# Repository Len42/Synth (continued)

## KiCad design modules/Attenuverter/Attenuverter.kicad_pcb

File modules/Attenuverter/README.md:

# Dual Attenuverter

## 4HP Eurorack Module

### Features
- Gain knob multiplies the input signal by 2 when turned to max and by -1 (i.e. inverted) when turned all the way down.
- Offset knob adds an offset voltage in the range of -5 V to +5 V.
- Channel 1's input is normalled from +5 V so it can be used as an adjustable CV source.
- Channel 2's input is normalled from channel 1's input.
- If channel 1's output is not patched, it is normalled to mix with channel 2's output. (Please note that this can cause unintended results if channel 2 is used without using channel 1.)

### Notes
For best results, the gain potentiometers (RV1 & RV3) should be very close to 100 kΩ. The pots specified for this project have a tolerance of 20% so I recommend measuring a few and selecting the most accurate ones.

PCB layouts are provided in KiCad and gerber formats. A PCB layout for a drilled front panel (with no labels) is also included.

The PCBs that I used can be ordered from OSH Park. The designs are here:
- [Front panel](https://oshpark.com/shared_projects/6utvepvX)
- [Controls board](https://oshpark.com/shared_projects/9pQK8wer)
- [Main board](https://oshpark.com/shared_projects/1qgK0ORb)

Please note that I am a hobbyist, not a trained electronics engineer. No guarantees!

### Software Used

* [KiCad](https://www.kicad.org/) 6.0.6

<hr /><div><div style="float:left; padding-right:10px;"></div><div style="xfloat:left; padding-left:10px;"><br />© 2022 Len Popp CC BY<br />This work is licensed under a <a rel="license" href="http://creativecommons.org/licenses/by/4.0/">Creative Commons Attribution 4.0 International License</a>.</div></div>

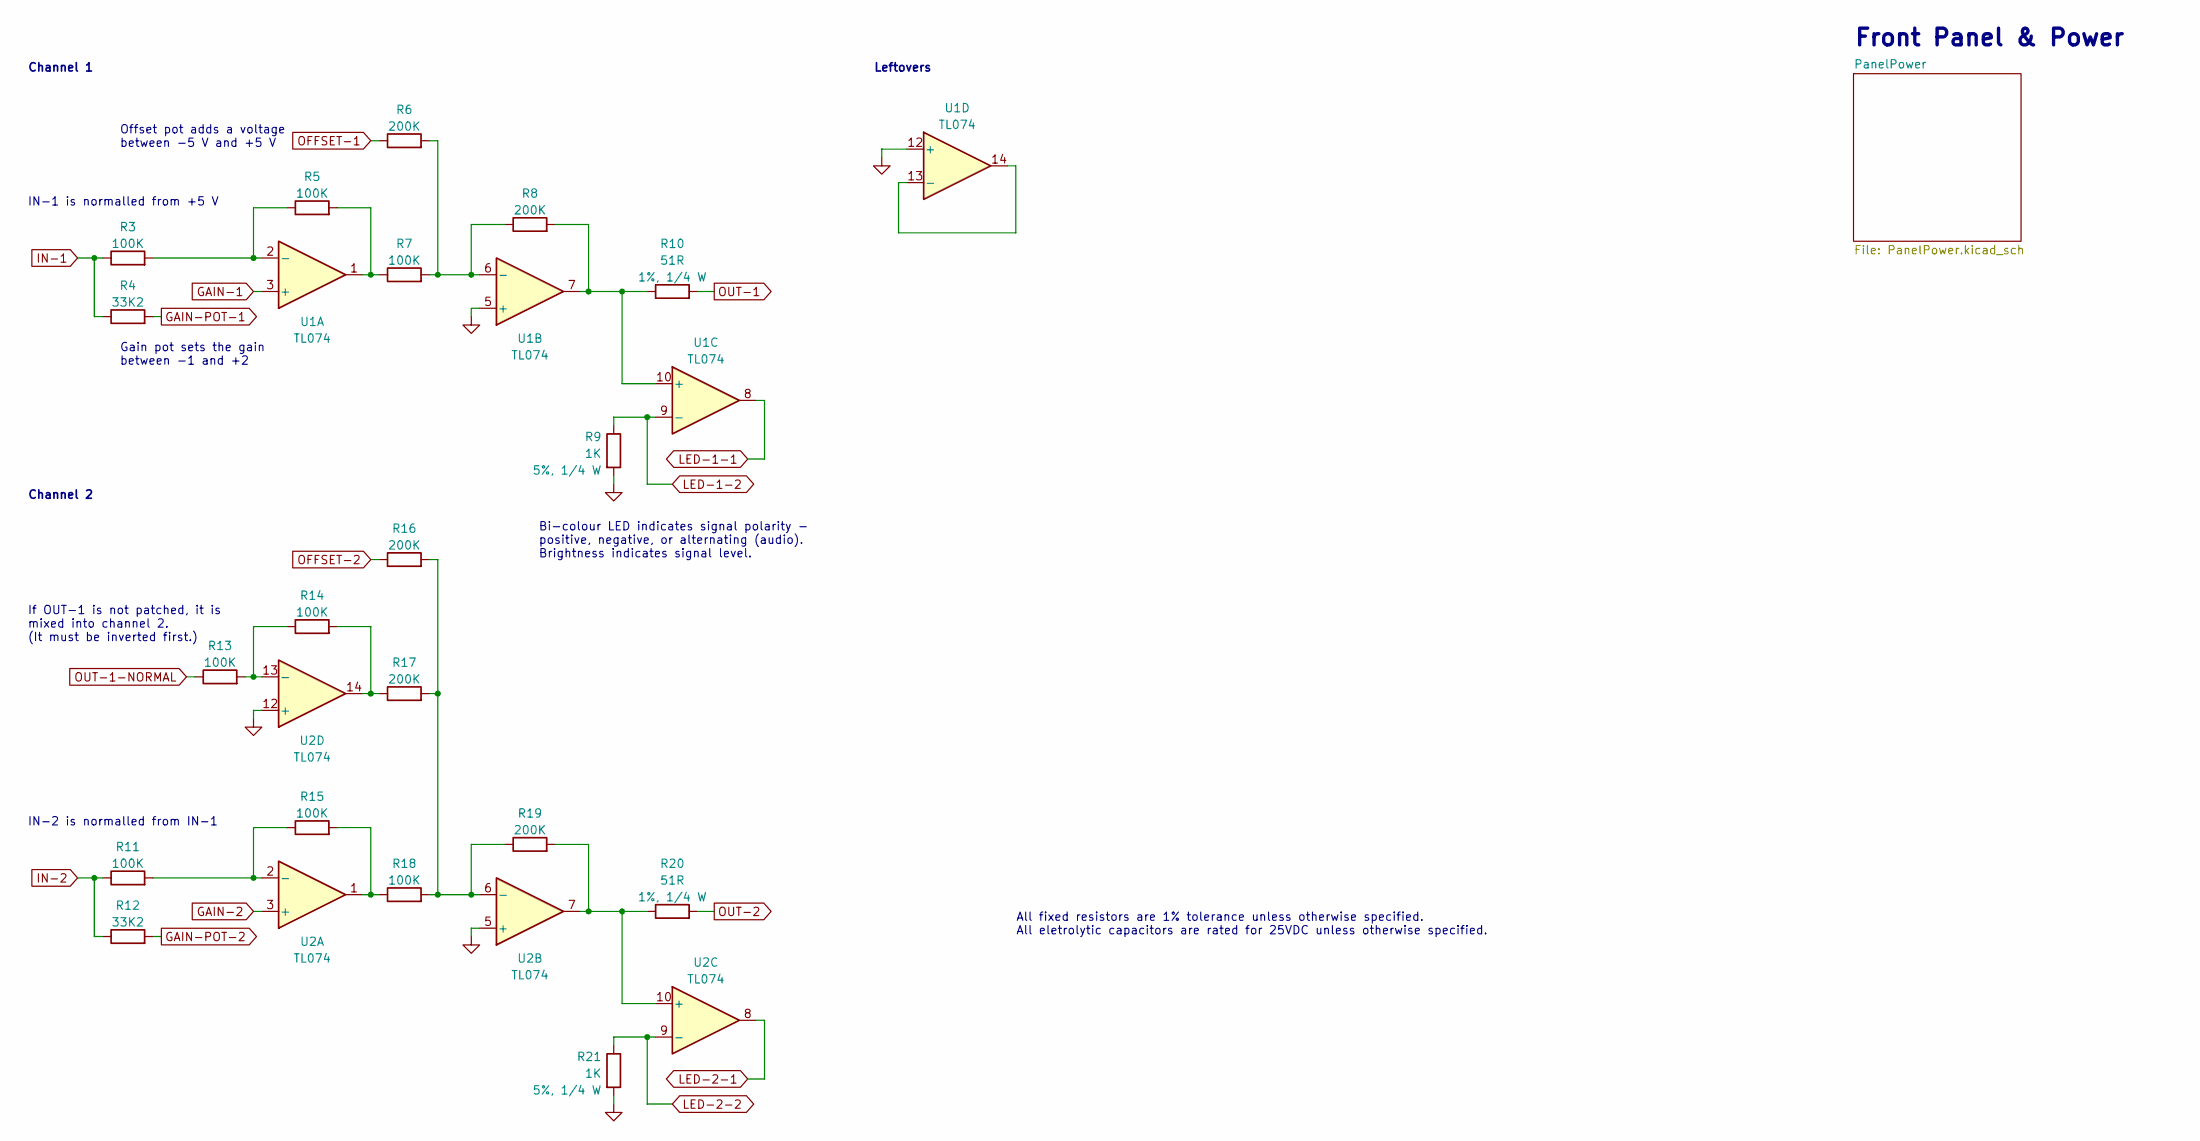
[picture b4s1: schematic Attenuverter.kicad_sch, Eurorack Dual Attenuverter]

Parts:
R3, R5, R7, R11, R13, R14, R15, R18: 100K; R_Axial_DIN0207_L6.3mm_D2.5mm_P7.62mm_Horizontal; ManufacturerPartNum MFR-12FRF52-100K
R4, R12: 33K2; R_Axial_DIN0207_L6.3mm_D2.5mm_P10.16mm_Horizontal; ManufacturerPartNum MFR-25FRF52-33K2
R6, R8, R16, R17, R19: 200K; R_Axial_DIN0207_L6.3mm_D2.5mm_P7.62mm_Horizontal; ManufacturerPartNum MFR-12FTF52-200K
R9, R21: 1K; R_Axial_DIN0207_L6.3mm_D2.5mm_P10.16mm_Horizontal; ManufacturerPartNum CCF071K00JKE36
R10, R20: 51R; R_Axial_DIN0207_L6.3mm_D2.5mm_P10.16mm_Horizontal; ManufacturerPartNum MFR-25FBF52-51R
U1, U2: TL074; DIP-14_W7.62mm; ManufacturerPartNum TL074BCN

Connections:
GAIN-1: U1.3 (+); also elsewhere on the board
GAIN-2: U2.3 (+); also elsewhere on the board
GAIN-POT-1: R4.2; also elsewhere on the board
GAIN-POT-2: R12.2; also elsewhere on the board
GND: R9.2, R21.2, U1.5 (+), U1.12 (+), U2.5 (+), U2.12 (+); also elsewhere on the board
IN-1: R3.1, R4.1; also elsewhere on the board
IN-2: R11.1, R12.1; also elsewhere on the board
LED-1-1: U1.8; also elsewhere on the board
LED-1-2: R9.1, U1.9 (-); also elsewhere on the board
LED-2-1: U2.8; also elsewhere on the board
LED-2-2: R21.1, U2.9 (-); also elsewhere on the board
unnamed: R3.2, R5.1, U1.2 (-)
unnamed: R5.2, R7.1, U1.1
unnamed: R6.2, R7.2, R8.1, U1.6 (-)
unnamed: R8.2, R10.1, U1.7, U1.10 (+)
unnamed: R11.2, R15.1, U2.2 (-)
unnamed: R13.2, R14.1, U2.13 (-)
unnamed: R14.2, R17.1, U2.14
unnamed: R15.2, R18.1, U2.1
unnamed: R16.2, R17.2, R18.2, R19.1, U2.6 (-)
unnamed: R19.2, R20.1, U2.7, U2.10 (+)
unnamed: U1.13 (-), U1.14
OFFSET-1: R6.1; also elsewhere on the board
OFFSET-2: R16.1; also elsewhere on the board
OUT-1: R10.2; also elsewhere on the board
OUT-1-NORMAL: R13.1; also elsewhere on the board
OUT-2: R20.2; also elsewhere on the board

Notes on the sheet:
IN-2 is normalled from IN-1
All fixed resistors are 1% tolerance unless otherwise specified. All eletrolytic capacitors are rated for 25VDC unless otherwise specified.
Bi-colour LED indicates signal polarity - positive, negative, or alternating (audio). Brightness indicates signal level.
Gain pot sets the gain between -1 and +2
IN-1 is normalled from +5 V
If OUT-1 is not patched, it is mixed into channel 2. (It must be inverted first.)
Front Panel & Power
Offset pot adds a voltage between -5 V and +5 V
Channel 1
Channel 2
Leftovers

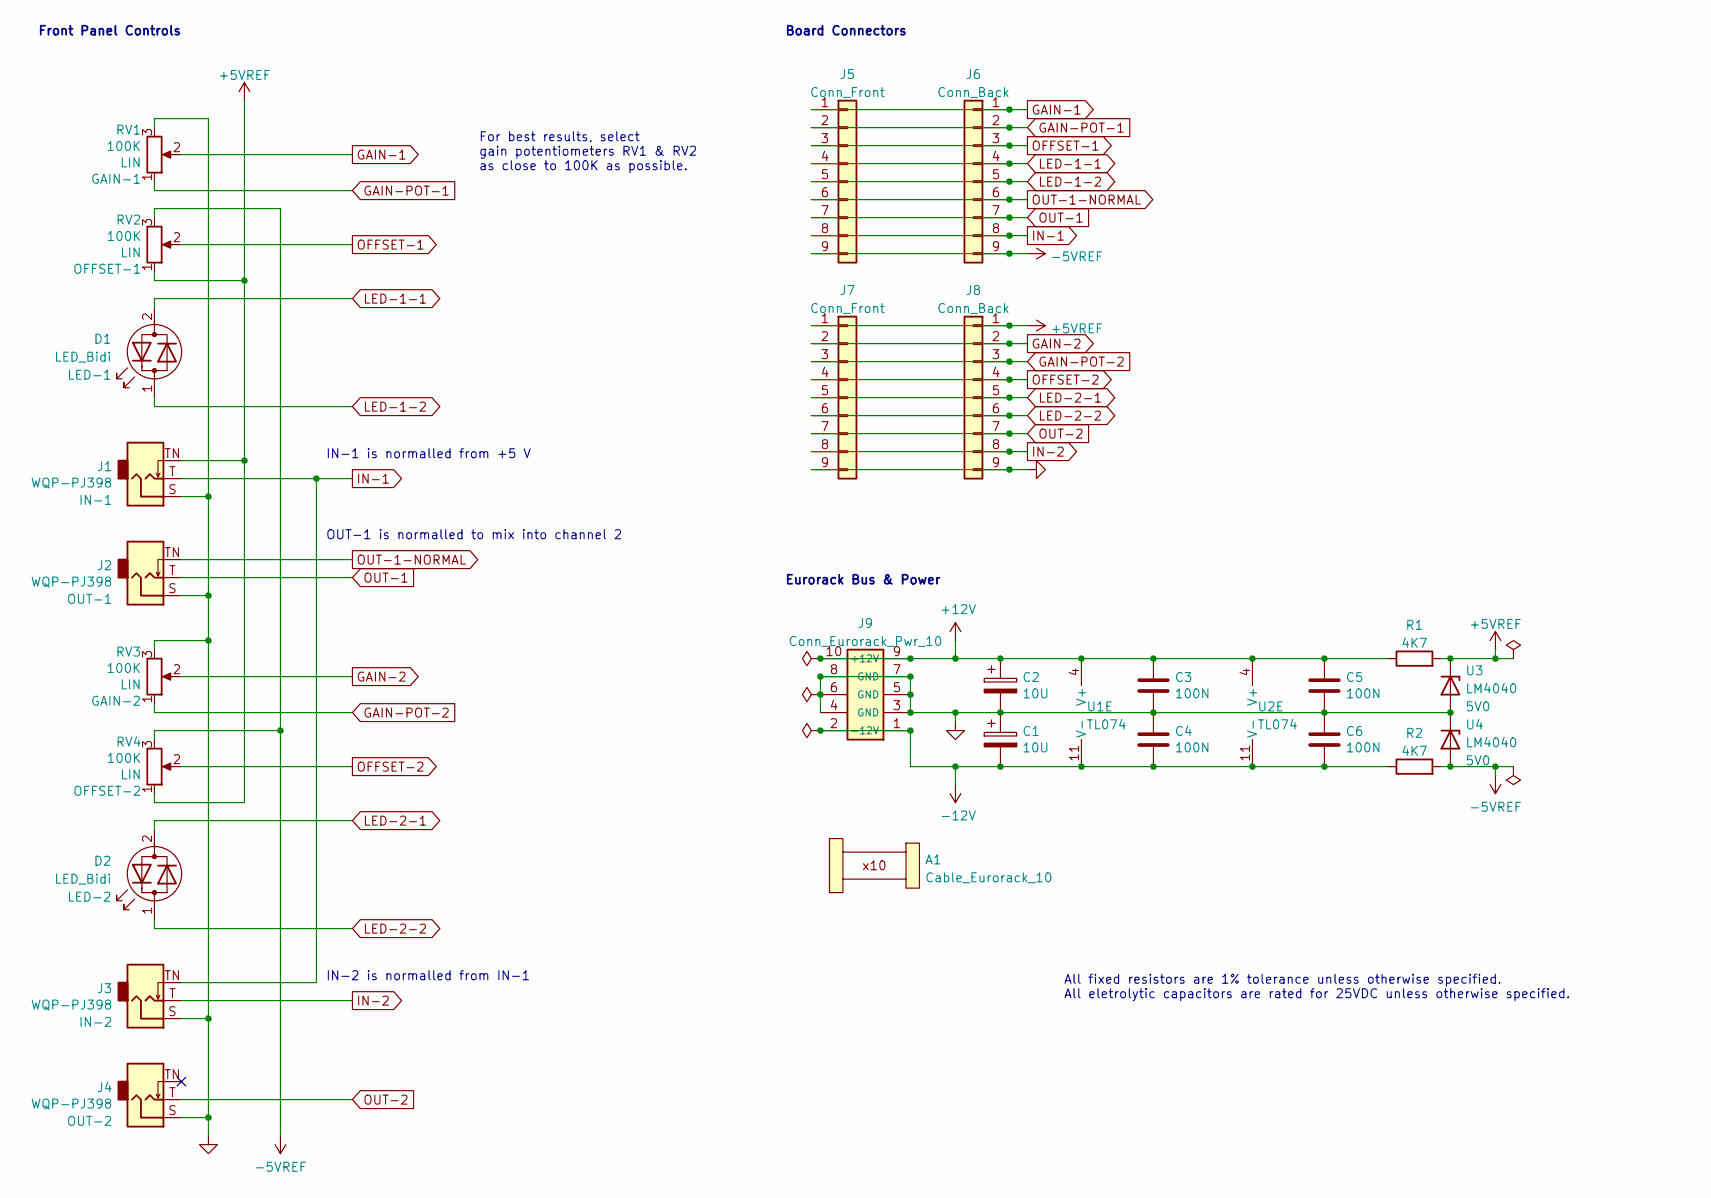
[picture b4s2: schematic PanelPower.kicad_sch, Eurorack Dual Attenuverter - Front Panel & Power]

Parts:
A1: Cable_Eurorack_10; NoFootprint
C1, C2: 10U; CP_Radial_D5.0mm_P2.50mm; ManufacturerPartNum ECE-A1VKS100I
C3, C4, C5, C6: 100N; C_Disc_D5.0mm_W2.5mm_P2.50mm; ManufacturerPartNum FG18X7R1H104KNT06
D1, D2: LED_Bidi; LED_D3.0mm; ManufacturerPartNum WP937GYW
J1, J2, J3, J4: WQP-PJ398; Jack_3.5mm_QingPu_WQP-PJ398SM_Vertical; ManufacturerPartNum PJ398SM / WQP518MA
J5, J7: Conn_Front; PinSocket_1x09_P2.54mm_Vertical
J6, J8: Conn_Back; PinHeader_1x09_P2.54mm_Horizontal
J9: Conn_Eurorack_Pwr_10; IDC-Header-Eurorack-10-TH; ManufacturerPartNum 61201021621
R1, R2: 4K7; R_Axial_DIN0207_L6.3mm_D2.5mm_P7.62mm_Horizontal; ManufacturerPartNum MFR-12FTF52-4K7
RV1, RV2, RV3, RV4: 100K; Potentiometer_Alpha_RD901F-40-00D_Single_Vertical; ManufacturerPartNum RD901F-*
U1, U2: TL074; DIP-14_W7.62mm; ManufacturerPartNum TL074BCN
U3, U4: LM4040; TO-92-2_Inline; ManufacturerPartNum LM4040BIZ-5.0/NOPB

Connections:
+5VREF: J1.TN, J7.1, J8.1, R1.2, RV2.1, RV4.1, U3.1 (K)
+12V: C2.1, C3.1, C5.1, J9.9 (+12V), J9.10, R1.1, U1.4 (V+), U2.4 (V+)
-5VREF: J5.9, J6.9, R2.2, RV2.3, RV4.3, U4.2 (A)
-12V: C1.2, C4.2, C6.2, J9.1 (-12V), J9.2, R2.1, U1.11 (V-), U2.11 (V-)
GAIN-1: J5.1, J6.1, RV1.2; also elsewhere on the board
GAIN-2: J7.2, J8.2, RV3.2; also elsewhere on the board
GAIN-POT-1: J5.2, J6.2, RV1.1; also elsewhere on the board
GAIN-POT-2: J7.3, J8.3, RV3.1; also elsewhere on the board
GND: C1.1, C2.2, C3.2, C4.1, C5.2, C6.1, J1.S, J2.S, J3.S, J4.S, J7.9, J8.9, J9.3 (GND), J9.4, J9.5 (GND), J9.6, J9.7 (GND), J9.8, RV1.3, RV3.3, U3.2 (A), U4.1 (K); also elsewhere on the board
IN-1: J1.T, J3.TN, J5.8, J6.8; also elsewhere on the board
IN-2: J3.T, J7.8, J8.8; also elsewhere on the board
LED-1-1: D1.2, J5.4, J6.4; also elsewhere on the board
LED-1-2: D1.1, J5.5, J6.5; also elsewhere on the board
LED-2-1: D2.2, J7.5, J8.5; also elsewhere on the board
LED-2-2: D2.1, J7.6, J8.6; also elsewhere on the board
OFFSET-1: J5.3, J6.3, RV2.2; also elsewhere on the board
OFFSET-2: J7.4, J8.4, RV4.2; also elsewhere on the board
OUT-1: J2.T, J5.7, J6.7; also elsewhere on the board
OUT-1-NORMAL: J2.TN, J5.6, J6.6; also elsewhere on the board
OUT-2: J4.T, J7.7, J8.7; also elsewhere on the board

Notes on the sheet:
IN-1 is normalled from +5 V
All fixed resistors are 1% tolerance unless otherwise specified. All eletrolytic capacitors are rated for 25VDC unless otherwise specified.
Eurorack Bus & Power
For best results, select gain potentiometers RV1 & RV2 as close to 100K as possible.
Board Connectors
IN-2 is normalled from IN-1
Front Panel Controls
OUT-1 is normalled to mix into channel 2

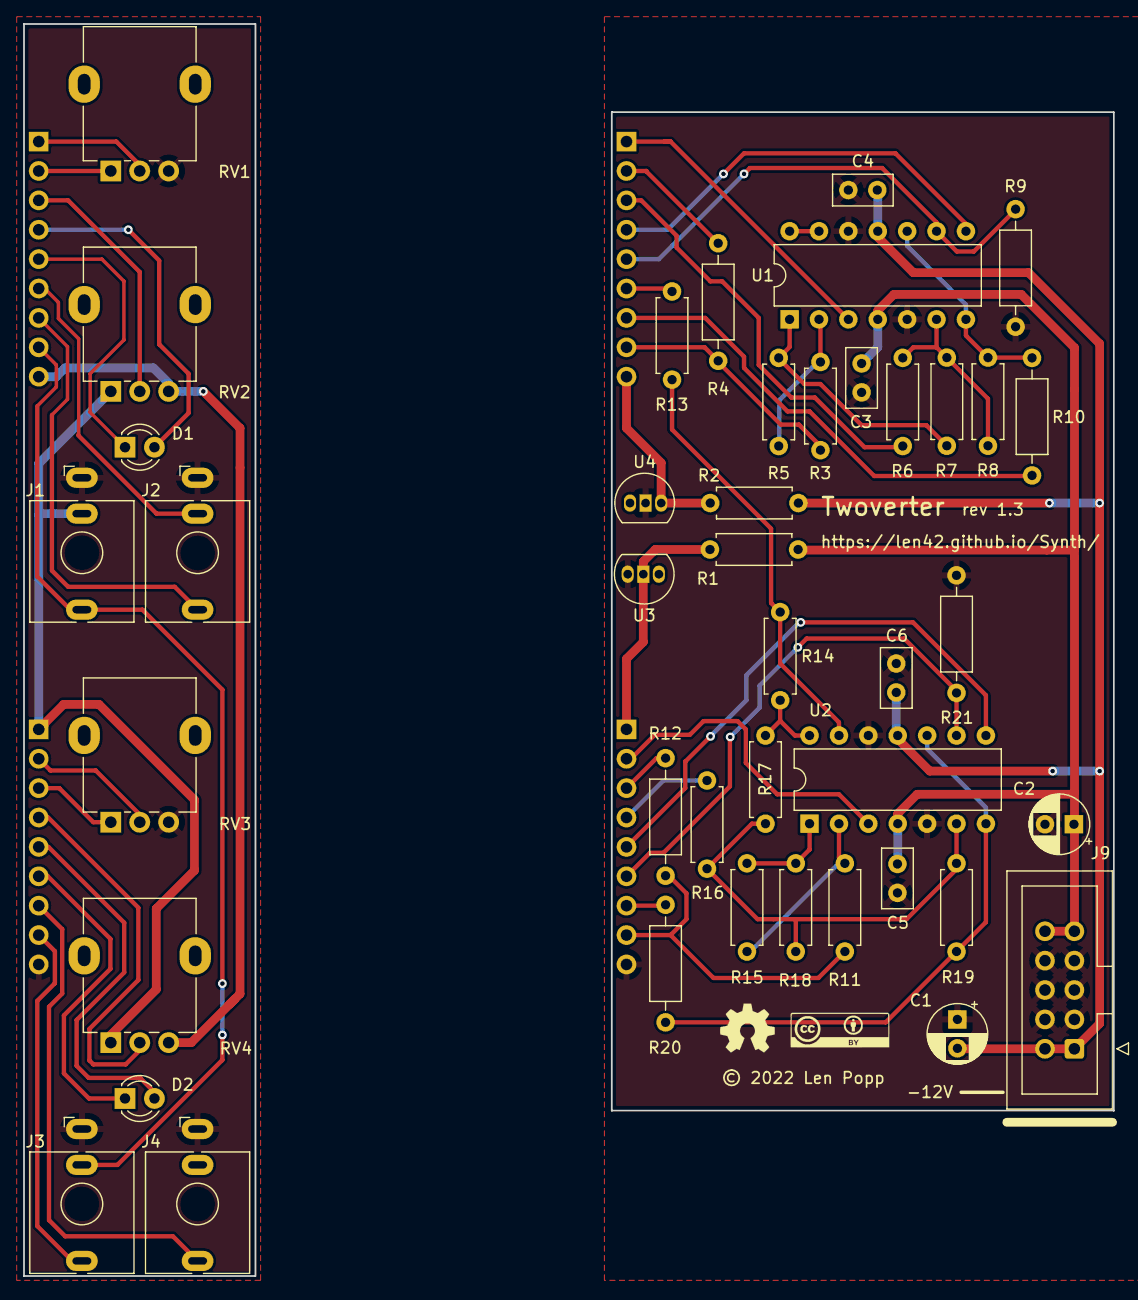
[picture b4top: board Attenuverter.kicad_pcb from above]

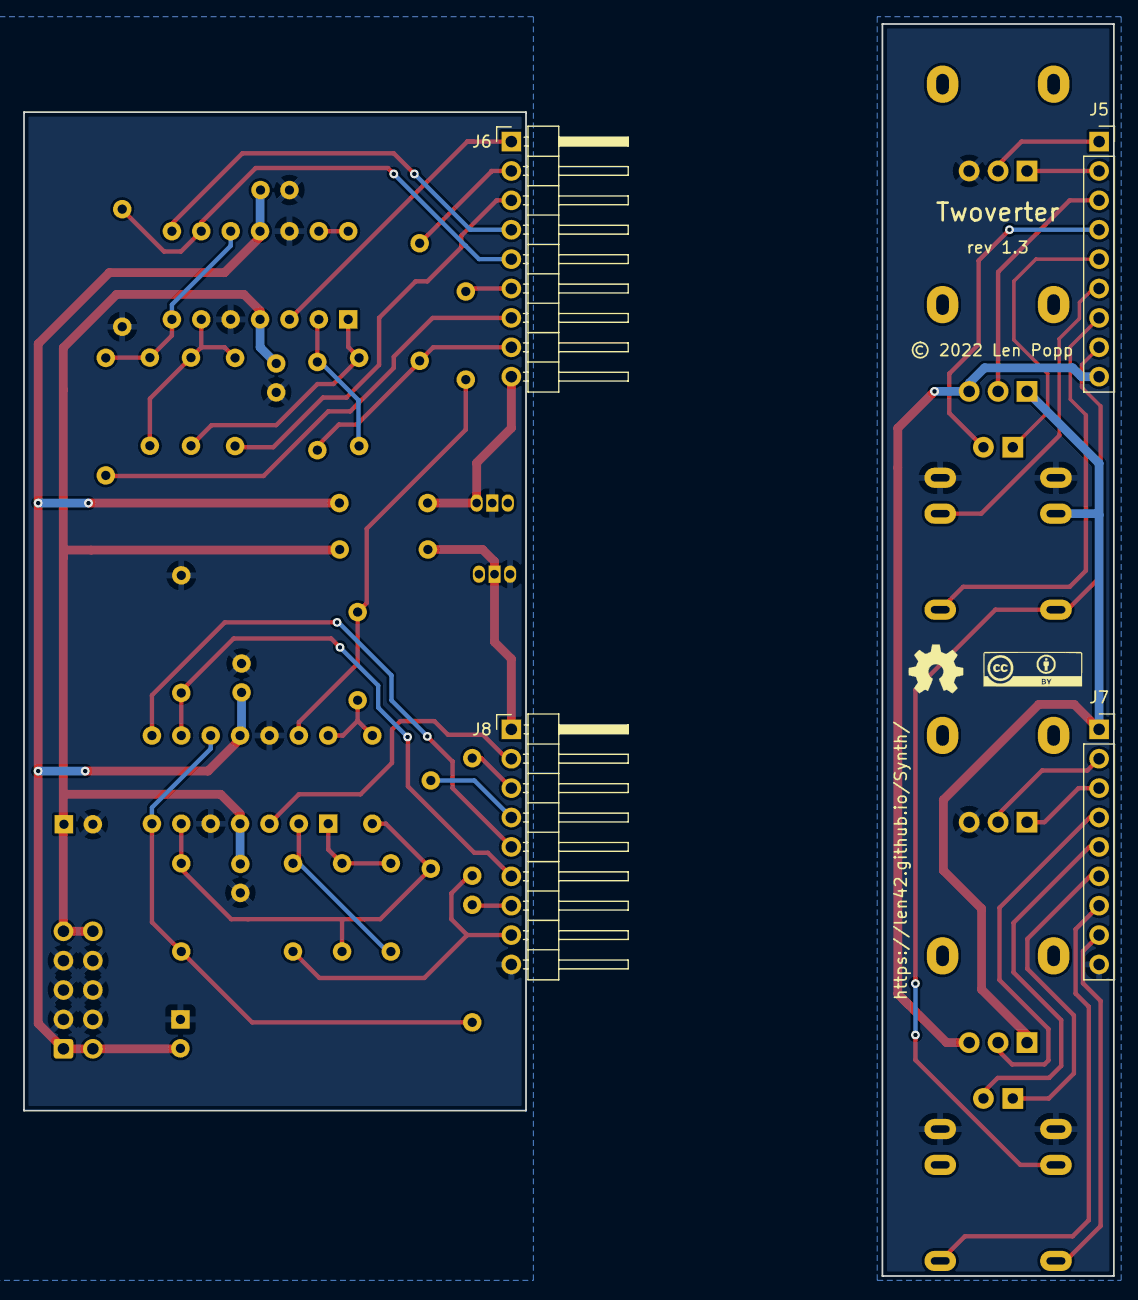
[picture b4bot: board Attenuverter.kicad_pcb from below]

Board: 2 copper layers, 94.2 x 108.2 mm, 50 parts (6 on the bottom side), 31 nets.

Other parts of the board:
G1, G2: Logo_CC_BY
G3, G4: Logo_OSHW

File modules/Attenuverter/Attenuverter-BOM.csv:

Ref,Qty,Value,Value2,Note,Description,Datasheet,Manufacturer,ManuPartNum,Distributor1,DistributorPartNum1,DistributorPartLink1,Distributor2,DistributorPartNum2,DistributorPartLink2,Distributor3,DistributorPartNum3,DistributorPartLink3
"A1","1","Cable_Eurorack_10","","Length as required","Eurorack 16-10 pin power cable","","","","Thonk","","https://www.thonk.co.uk/shop/eurorack-power-cables/","SynthCube","","https://synthcube.com/cart/eurorack-ribbon-power-cables","Modular Addict","","https://modularaddict.com/parts/eurorack-power-cables-1"
"C1 C2","2","10U","35 VDC","12 V decoupling","Capacitor - Electrolytic - 12 V decoupling","https://www.mouser.ca/datasheet/2/315/ABA0000C1059-947582.pdf","Panasonic","ECE-A1VKS100I","Mouser","667-ECE-A1VKS100I","https://www.mouser.ca/ProductDetail/667-ECE-A1VKS100I","Thonk","Group_Eurorack_DIY_Essential","https://www.thonk.co.uk/shop/eurorack-diy-essentials/","","",""
"C3 C4 C5 C6","4","100N","","IC decoupling","Capacitor - Ceramic - IC decoupling","https://product.tdk.com/system/files/dam/doc/product/capacit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","TDK","FG18X7R1H104KNT06","Mouser","810-FG18X7R1H104KNT6","https://www.mouser.ca/ProductDetail/810-FG18X7R1H104KNT6","","","","","",""
"D1 D2","2","LED_Bidi","","","Dual LED, red and green, common cathode on pin 2","https://www.mouser.ca/datasheet/2/216/WP937GYW-49419.pdf","Kingbright","WP937GYW","Mouser","604-WP937GYW","https://www.mouser.ca/ProductDetail/Kingbright/WP937GYW?qs=p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","","","","","",""
"J1 J2 J3 J4","4","WQP-PJ398","","","Audio Jack, 2 Poles (Mono / TS), Switched T Pole (Normalling), QingPu / Thonkiconn","http://www.qingpu-electronics.com/en/products/WQP-PJ398SM-362.html","QingPu / Thonk","PJ398SM / WQP518MA","Thonk","PJ398SM","https://www.thonk.co.uk/shop/thonkiconn/","SynthCube","WQP518MA","https://synthcube.com/cart/3-5mm-euro-jacks","Adafruit","4031","https://www.adafruit.com/product/4031"
"J5 J7","2","Conn_Front","","","Generic connector, single row, 01x09, script generated (kicad-library-utils/schlib/autogen/connector/)","","","","Adafruit","598","https://www.adafruit.com/product/598","Mouser","710-61303211821","https://www.mouser.ca/ProductDetail/Wurth-Elektronik/6130321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","","",""
"J6 J8","2","Conn_Back","","","Generic connector, single row, 01x09, script generated (kicad-library-utils/schlib/autogen/connector/)","","","","Adafruit","1540","https://www.adafruit.com/product/1540","Mouser","649-1012937993601BLF","https://www.mouser.ca/ProductDetail/Amphenol-FCI/10129379-93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","","",""
"J9","1","Conn_Eurorack_Pwr_10","","","Eurorack 10-pin board power connector","https://www.mouser.ca/datasheet/2/445/61201021621-1717731.pdf","Wurth Elektronik","61201021621","Mouser","710-61201021621","https://www.mouser.ca/ProductDetail/Wurth-Elektronik/6120102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","Thonk","","https://www.thonk.co.uk/shop/eurorack-diy-essentials/","","",""
"R1 R2","2","4K7","1%, 1/6 W","","Resistor","https://www.mouser.ca/datasheet/2/447/Yageo_LR_MFR_1-1714151.pdf","YAGEO","MFR-12FTF52-4K7","Mouser","603-MFR-12FTF52-4K7","https://www.mouser.ca/ProductDetail/YAGEO/MFR-12FTF52-4K7?qs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","","","","","",""
"R3 R5 R7 R11 R13 R14 R15 R18","8","100K","1%, 1/6 W","","Resistor","https://www.mouser.ca/datasheet/2/447/Yageo_LR_MFR_1-1714151.pdf","YAGEO","MFR-12FRF52-100K","Mouser","603-MFR-12FRF52100K","https://www.mouser.ca/ProductDetail/YAGEO/MFR-12FRF52-100K?q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","","","","","",""
"R4 R12","2","33K2","1%, 1/6 W","","Resistor","https://www.mouser.ca/datasheet/2/447/Yageo_LR_MFR_1-1714151.pdf","YAGEO","MFR-25FRF52-33K2","Mouser","603-MFR-25FRF5233K2","https://www.mouser.ca/ProductDetail/?qs=5furm%2FeQHzT8SPOPrj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","","","","","",""
"R6 R8 R16 R17 R19","5","200K","1%, 1/6 W","","Resistor","https://www.mouser.ca/datasheet/2/447/Yageo_LR_MFR_1-1714151.pdf","YAGEO","MFR-12FTF52-200K","Mouser","603-MFR-12FTF52-200K","https://www.mouser.ca/ProductDetail/YAGEO/MFR-12FTF52-200K?q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","","","","","",""
"R9 R21","2","1K","5%, 1/4 W","Output limiting","Resistor","https://www.mouser.ca/datasheet/2/427/ccf07-1762725.pdf","Vishay / Dale","CCF071K00JKE36","Mouser","71-CCF071K00JKE36","https://www.mouser.ca/ProductDetail/Vishay-Dale/CCF071K00JKE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","","","","","",""
"R10 R20","2","51R","1%, 1/4 W","Output limiting","Resistor","https://www.mouser.ca/datasheet/2/447/Yageo_LR_MFR_1-1714151.pdf","YAGEO","MFR-25FBF52-51R","Mouser","603-MFR-25FBF52-51R","https://www.mouser.ca/ProductDetail/?qs=oAGoVhmvjhzVx2bdEH1T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","","","","","",""
"RV1 RV2 RV3 RV4","4","100K","LIN","","Potentiometer","https://www.mouser.ca/datasheet/2/13/alpha_taiwan_08192019_R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","Alpha","RD901F-*","Thonk","Group_Pot_Alpha_6.35mm","https://www.thonk.co.uk/shop/alpha-9mm-pots/","Mouser","311-1940F-*","https://www.mouser.ca/c/passive-components/potentiometers-tr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","SynthCube","9MMALPHAPOTMSTR","https://synthcube.com/cart/alpha-9mm-potentiometer-right-ang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"
"U1 U2","2","TL074","","","Quad Low-Noise JFET-Input Operational Amplifiers, DIP-14/SOIC-14","http://www.ti.com/lit/ds/symlink/tl071.pdf","Texas Instruments","TL074BCN","Mouser","595-TL074BCN","https://www.mouser.ca/ProductDetail/?qs=vxEfx8VrU7BHurOY5iQd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","","","","","",""
"U3 U4","2","LM4040","5V0","","LM4040 shunt voltage reference","https://www.ti.com/lit/ds/symlink/lm4040-n.pdf?ts=1622551591255","Texas Instruments","LM4040BIZ-5.0/NOPB","Mouser","926-LM4040BIZ50NOPB","https://www.mouser.ca/ProductDetail/Texas-Instruments/LM4040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","","","","","",""

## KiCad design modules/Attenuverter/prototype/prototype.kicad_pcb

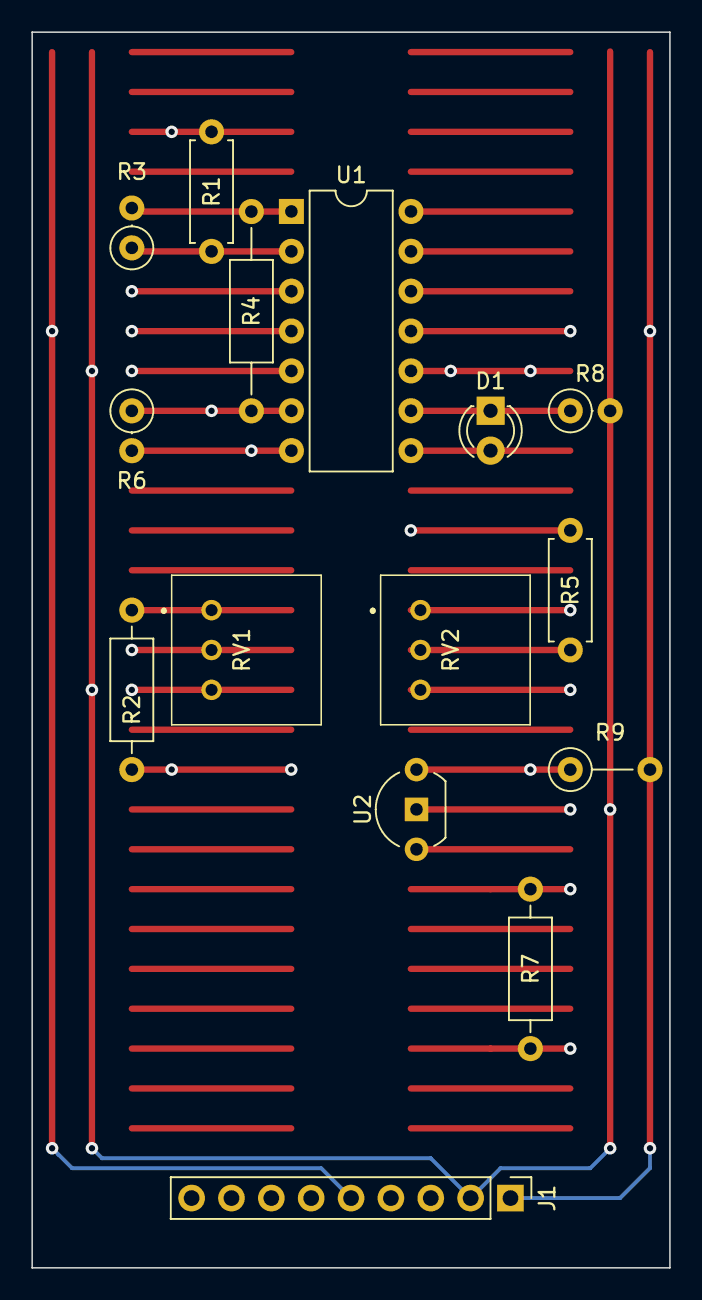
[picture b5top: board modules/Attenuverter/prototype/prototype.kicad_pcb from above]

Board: 6 copper layers, 40.6 x 78.7 mm, 15 parts (0 on the bottom side), 16 nets.

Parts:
D1: LED_Bidi; LED_D3.0mm
J1: Conn_01x09; PinHeader_1x09_P2.54mm_Vertical
R1: 100K; R_Axial_DIN0207_L6.3mm_D2.5mm_P7.62mm_Horizontal
R2: 33K2; R_Axial_DIN0207_L6.3mm_D2.5mm_P10.16mm_Horizontal
R3: 100K; SB_Gen_1
R4: 100K; SB_Gen_5
R5: 200K; R_Axial_DIN0207_L6.3mm_D2.5mm_P7.62mm_Horizontal
R6: 200K; SB_Gen_1
R7: 51R; R_Axial_DIN0207_L6.3mm_D2.5mm_P10.16mm_Horizontal
R8: 1K; SB_Gen_1
R9: 4K7; SB_Gen_2
RV1, RV2: 100K; Potentiometer_Bourns_3310R_Top
U1: TL074; DIP-14_W7.62mm
U2: LM4040; TO-92-2_Wide

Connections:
+5V: J1.7, RV2.1
+12V: J1.5, U1.4 (V+)
-5VREF: R9.1, RV2.3, U2.2 (A)
-12V: J1.1, R9.2, U1.11 (V-)
GND: J1.2, R8.2, RV1.3, U1.5 (+), U2.1 (K)
IN: J1.4, R1.1, R2.1
unnamed: R1.2, R3.1, U1.2 (-)
unnamed: R3.2, R4.1, U1.1
unnamed: R4.2, R5.2, R6.1, U1.6 (-)
unnamed: R6.2, R7.1, U1.7, U1.10 (+)
unnamed: D1.1, R8.1, U1.9 (-)
unnamed: D1.2, U1.8
unnamed: R2.2, RV1.1
unnamed: R5.1, RV2.2
unnamed: RV1.2, U1.3 (+)
OUT: J1.3, R7.2

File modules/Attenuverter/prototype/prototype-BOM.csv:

Ref,Qty,Value,Value2,Note,Description,Datasheet,Manufacturer,ManuPartNum,Distributor1,DistributorPartNum1,DistributorPartLink1
"D1","1","LED_Bidi","","","Dual LED, red and green, common cathode on pin 2","https://www.mouser.ca/datasheet/2/216/WP937GYW-49419.pdf","Kingbright","WP937GYW","Mouser","604-WP937GYW","https://www.mouser.ca/ProductDetail/Kingbright/WP937GYW?qs=p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"
"R1 R3 R4","3","100K","1%, 1/6 W","","Resistor","https://www.mouser.ca/datasheet/2/447/Yageo_LR_MFR_1-1714151.pdf","YAGEO","MFR-12*","Mouser","603-MFR-12*","https://www.mouser.ca/c/?m=YAGEO&power+rating=166+mW+(1%2f6+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"
"R2","1","33K2","","","Resistor","https://www.mouser.ca/datasheet/2/447/Yageo_LR_MFR_1-1714151.pdf","","","Mouser","",""
"R5 R6","2","200K","1%, 1/6 W","","Resistor","https://www.mouser.ca/datasheet/2/447/Yageo_LR_MFR_1-1714151.pdf","YAGEO","MFR-12*","Mouser","603-MFR-12*","https://www.mouser.ca/c/?m=YAGEO&power+rating=166+mW+(1%2f6+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"
"R7","1","51R","1%, 1/4 W","Output limiting","Resistor","https://www.mouser.ca/datasheet/2/447/Yageo_LR_MFR_1-1714151.pdf","YAGEO","MFR-25FBF52-51R","Mouser","603-MFR-25FBF52-51R","https://www.mouser.ca/ProductDetail/?qs=oAGoVhmvjhzVx2bdEH1T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"
"R8","1","1K","5%, 1/4 W","Output limiting","Resistor","https://www.mouser.ca/datasheet/2/427/ccf07-1762725.pdf","Vishay / Dale","CCF071K00JKE36","Mouser","71-CCF071K00JKE36","https://www.mouser.ca/ProductDetail/Vishay-Dale/CCF071K00JKE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"
"R9","1","4K7","1%, 1/6 W","","Resistor","https://www.mouser.ca/datasheet/2/447/Yageo_LR_MFR_1-1714151.pdf","YAGEO","MFR-12*","Mouser","603-MFR-12*","https://www.mouser.ca/c/?m=YAGEO&power+rating=166+mW+(1%2f6+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"
"RV1 RV2","2","100K","","","Trim-potentiometer","https://www.mouser.ca/datasheet/2/54/3386-776606.pdf","Bourns","3386*","Mouser","652-3386*","https://www.mouser.ca/c/passive-components/resistors/variabl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"
"U1","1","TL074","","","Quad Low-Noise JFET-Input Operational Amplifiers, DIP-14/SOIC-14","http://www.ti.com/lit/ds/symlink/tl071.pdf","Texas Instruments","TL074BCN","Mouser","595-TL074BCN","https://www.mouser.ca/ProductDetail/?qs=vxEfx8VrU7BHurOY5iQd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"
"U2","1","LM4040","5V0","","LM4040 shunt voltage reference","https://www.ti.com/lit/ds/symlink/lm4040-n.pdf?ts=1622551591255","Texas Instruments","LM4040*","Mouser","","https://www.mouser.ca/c/semiconductors/integrated-circuits-i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"

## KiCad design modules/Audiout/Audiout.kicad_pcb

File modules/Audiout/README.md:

# Audiout - Stereo Output Module

## 4HP Eurorack Module

### Features
- _Input:_ Eurorack jacks for left & right channels, with left normalled to right for mono
- _Headphone output:_ 3.5 mm stereo headphone jack
- _Balanced stereo line output:_ 3.5 mm TRS jacks for left & right channels. Requires two cables with a 3.5 mm TRS plug on one end and either a 1/4 inch TRS or XLR plug on the other end.
- Separate level controls for headphone and line outputs.

### Notes
This module requires a 16-pin Eurorack power cable that supplies +5 V power in addition to +12 V and -12 V.

PCB layouts are provided in KiCad and gerber formats. A front panel design is included as a drilled PCB layout (with no labels or graphics).

The PCBs that I used can be ordered from OSH Park. The designs are here:
- [Front panel](https://oshpark.com/shared_projects/ir0qqB0Y)
- [Controls board](https://oshpark.com/shared_projects/OsCKzftx)
- [Main board](https://oshpark.com/shared_projects/VA7ex4FE)

Please note that I am a hobbyist, not a trained electronics engineer. No guarantees!

### Software Used
[KiCad](https://www.kicad.org/) 6.0.4

<hr /><div><div style="float:left; padding-right:10px;"></div><div style="xfloat:left; padding-left:10px;"><br />© 2022 Len Popp CC BY<br />This work is licensed under a <a rel="license" href="http://creativecommons.org/licenses/by/4.0/">Creative Commons Attribution 4.0 International License</a>.</div></div>

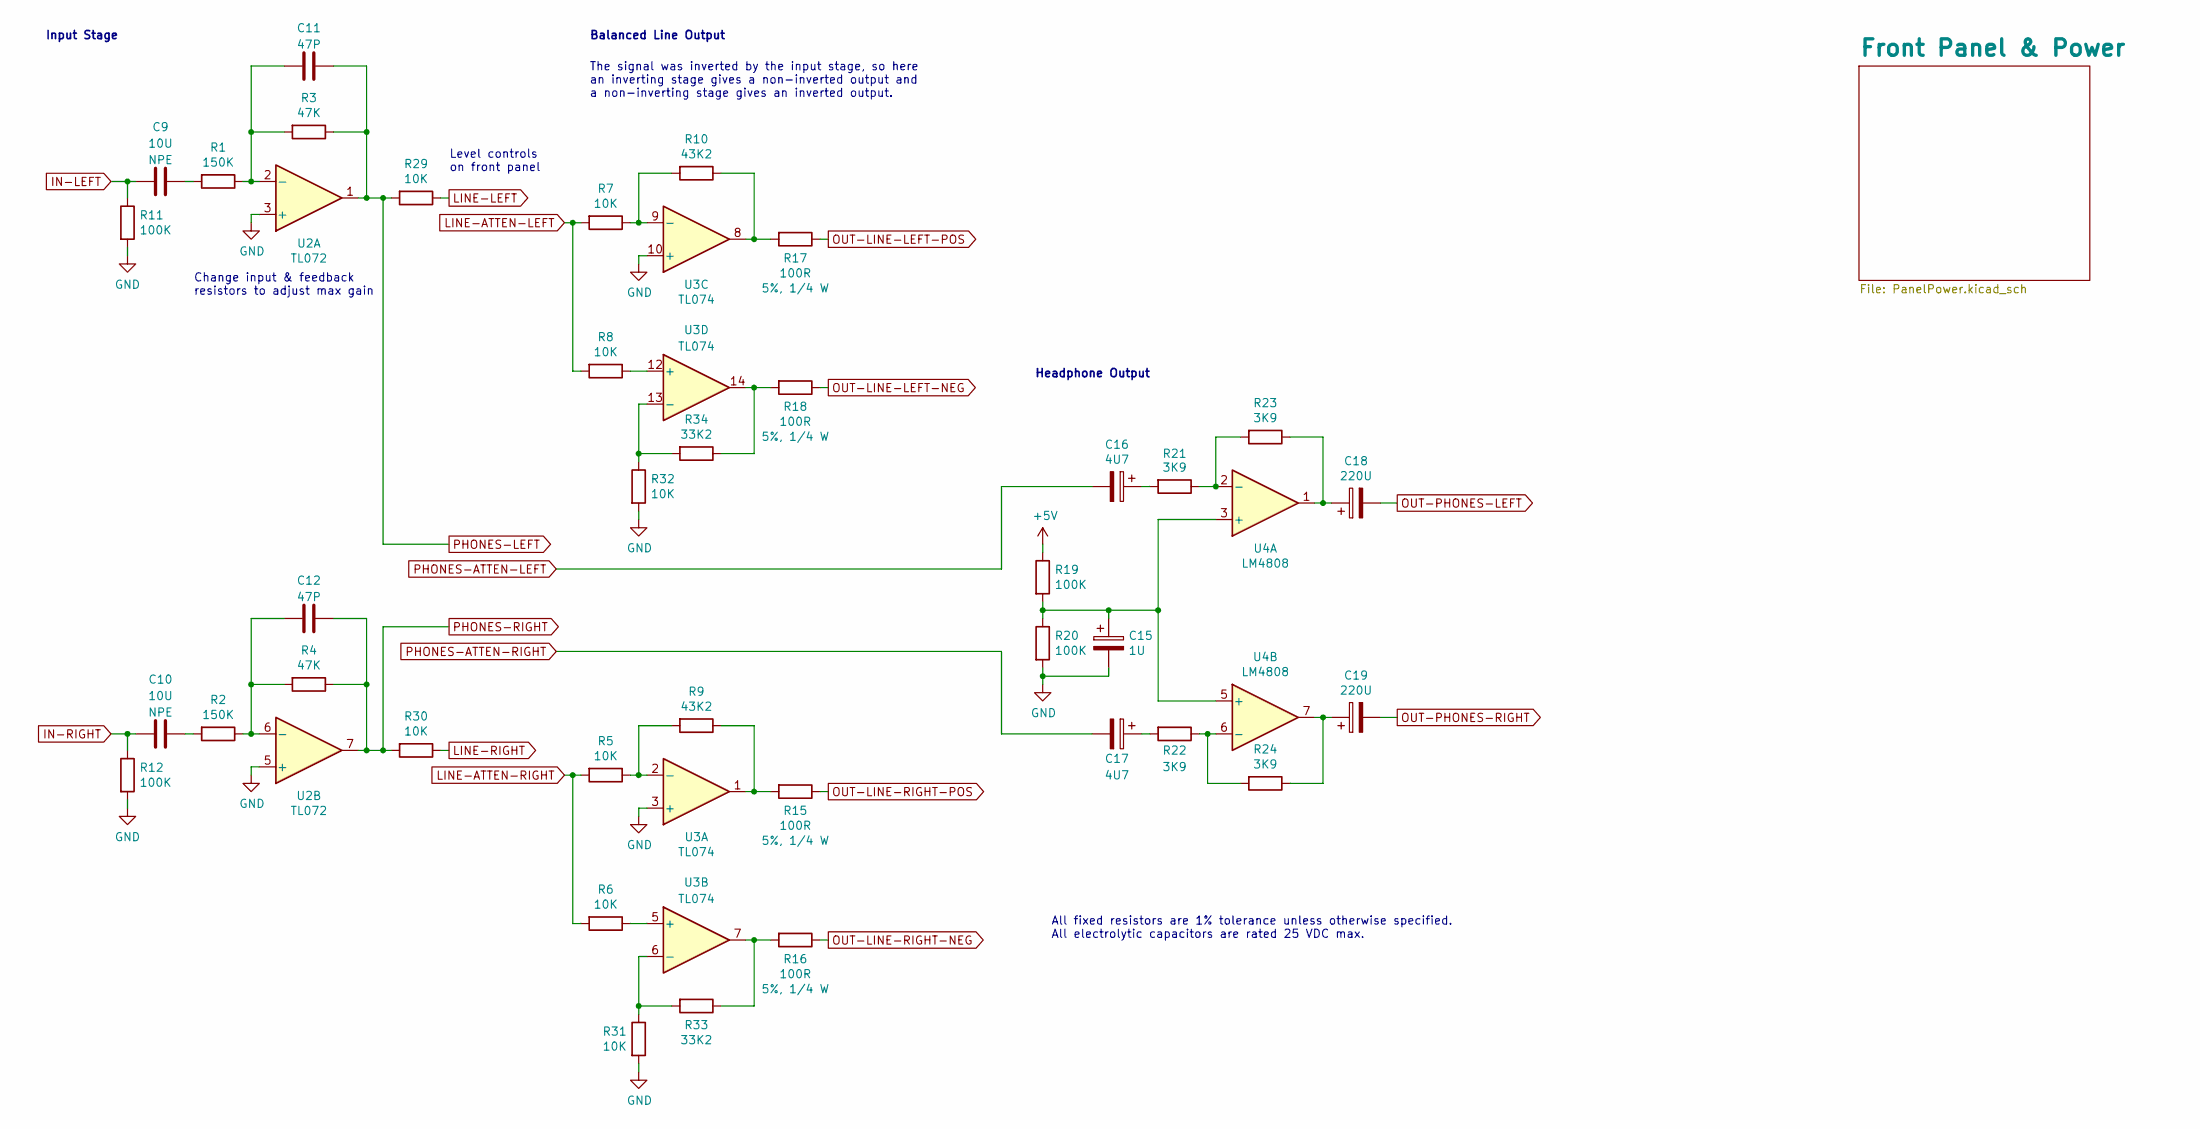
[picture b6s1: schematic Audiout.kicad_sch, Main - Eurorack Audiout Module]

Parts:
C9, C10: 10U; C_Radial_D5.0mm_H5.0mm_P2.50mm; ManufacturerPartNum ECE-A1EN100UI
C11, C12: 47P; C_Disc_D5.0mm_W2.5mm_P2.50mm; ManufacturerPartNum K470K15C0GH53L2
C15: 1U; CP_Radial_D5.0mm_P2.00mm; ManufacturerPartNum 50YXJ1M5X11
C16, C17: 4U7; CP_Radial_D4.0mm_P2.50mm; ManufacturerPartNum ECE-A1EKA4R7I
C18, C19: 220U; CP_Radial_D8.0mm_P3.50mm; ManufacturerPartNum EEU-EB1E221SJ
R1, R2: 150K; R_Axial_DIN0207_L6.3mm_D2.5mm_P7.62mm_Horizontal; ManufacturerPartNum MFR-12FTF52-150K
R3, R4: 47K; R_Axial_DIN0207_L6.3mm_D2.5mm_P7.62mm_Horizontal; ManufacturerPartNum MFR-12FTF52-47K
R5, R6, R7, R8, R29, R30, R31, R32: 10K; R_Axial_DIN0207_L6.3mm_D2.5mm_P7.62mm_Horizontal; ManufacturerPartNum MFR-12FRF52-10K
R9, R10: 43K2; R_Axial_DIN0207_L6.3mm_D2.5mm_P7.62mm_Horizontal; ManufacturerPartNum RN55D4322FRE6
R11, R12, R19, R20: 100K; R_Axial_DIN0207_L6.3mm_D2.5mm_P7.62mm_Horizontal; ManufacturerPartNum MFR-12FTF52-100K
R15, R16, R17, R18: 100R; R_Axial_DIN0207_L6.3mm_D2.5mm_P10.16mm_Horizontal; ManufacturerPartNum MFR-25FTF52-100R
R21, R22, R23, R24: 3K9; R_Axial_DIN0207_L6.3mm_D2.5mm_P7.62mm_Horizontal; ManufacturerPartNum MFR-12FTF52-3K9
R33, R34: 33K2; R_Axial_DIN0207_L6.3mm_D2.5mm_P7.62mm_Horizontal; ManufacturerPartNum RN55D3322FRE6
U2: TL072; DIP-8_W7.62mm; ManufacturerPartNum TL072BCP
U3: TL074; DIP-14_W7.62mm; ManufacturerPartNum TL074BCN
U4: LM4808; Breakout_DIP-SOIC-8_W7.62mm; ManufacturerPartNum LM4808MX/NOPB

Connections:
+5V: R19.1; also elsewhere on the board
GND: C15.2, R11.2, R12.2, R20.2, R31.2, R32.2, U2.3 (+), U2.5 (+), U3.3 (+), U3.10 (+); also elsewhere on the board
IN-LEFT: C9.2, R11.1; also elsewhere on the board
IN-RIGHT: C10.2, R12.1; also elsewhere on the board
LINE-ATTEN-LEFT: R7.2, R8.2; also elsewhere on the board
LINE-ATTEN-RIGHT: R5.2, R6.2; also elsewhere on the board
LINE-LEFT: R29.1; also elsewhere on the board
LINE-RIGHT: R30.1; also elsewhere on the board
unnamed: C9.1, R1.2
unnamed: C10.1, R2.2
unnamed: C11.2, R1.1, R3.2, U2.2 (-)
unnamed: C12.2, R2.1, R4.2, U2.6 (-)
unnamed: C15.1, R19.2, R20.1, U4.3 (+), U4.5 (+)
unnamed: C16.1, R21.2
unnamed: C17.1, R22.2
unnamed: C18.1, R23.1, U4.1
unnamed: C19.1, R24.1, U4.7
unnamed: R5.1, R9.2, U3.2 (-)
unnamed: R6.1, U3.5 (+)
unnamed: R8.1, U3.12 (+)
unnamed: R10.1, R17.2, U3.8
unnamed: R7.1, R10.2, U3.9 (-)
unnamed: R9.1, R15.2, U3.1
unnamed: R16.2, R33.1, U3.7
unnamed: R18.2, R34.1, U3.14
unnamed: R21.1, R23.2, U4.2 (-)
unnamed: R22.1, R24.2, U4.6 (-)
unnamed: R31.1, R33.2, U3.6 (-)
unnamed: R32.1, R34.2, U3.13 (-)
OUT-LINE-LEFT-NEG: R18.1; also elsewhere on the board
OUT-LINE-LEFT-POS: R17.1; also elsewhere on the board
OUT-LINE-RIGHT-NEG: R16.1; also elsewhere on the board
OUT-LINE-RIGHT-POS: R15.1; also elsewhere on the board
OUT-PHONES-LEFT: C18.2; also elsewhere on the board
OUT-PHONES-RIGHT: C19.2; also elsewhere on the board
PHONES-ATTEN-LEFT: C16.2; also elsewhere on the board
PHONES-ATTEN-RIGHT: C17.2; also elsewhere on the board
PHONES-LEFT: C11.1, R3.1, R29.2, U2.1; also elsewhere on the board
PHONES-RIGHT: C12.1, R4.1, R30.2, U2.7; also elsewhere on the board

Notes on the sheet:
Input Stage
Level controls on front panel
Change input & feedback resistors to adjust max gain
The signal was inverted by the input stage, so here an inverting stage gives a non-inverted output and a non-inverting stage gives an inverted output.
Headphone Output
Balanced Line Output
All fixed resistors are 1% tolerance unless otherwise specified. All electrolytic capacitors are rated 25 VDC max.
